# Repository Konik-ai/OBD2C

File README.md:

Designed using Kicad 8

Unlike harness box, OBD2-C doesn't use the relay. 

The purpose of it is to sniff CAN buses that are already present in OBD-2 port, similar to what white panda was doing in the past, but compatible with [OBD-C](https://github.com/commaai/neo/blob/master/car_harness/OBD-C.sch.pdf), though often only diagnostic CAN is populated on OBD-2.

The device exposes three CAN buses out of OBD-C:
- CAN0 (3, 11)
- CAN1 is routed to the JST (pin 2,3) connector (can be connected .e.g to [StepperServoCAN](https://github.com/dzid26/StepperServo-hardware)) and has optional 120ohm termination resistor (see jumpers).
Alternatively, bus 1 can be rerouted using jumpers as a GMLAN (obd pin 1) as in [white panda](https://comma-ai.medium.com/a-panda-and-a-cabana-how-to-get-started-car-hacking-with-comma-ai-b5e46fae8646) - but unlike [white panda](https://github.com/martiinezz/panda/blob/master/white-hw/README.md) it uses single wire [hack](https://canhacker.com/examples/gm-lan-single-wire-can-examples/) and is not tested
- CAN2 (pins 12, 13)
- CAN3 (pins 6, 14) - this one can be used e.g. as "[ELM327](https://github.com/commaai/panda/blob/master/examples/query_vin_and_stats.py)" or [vin](https://github.com/commaai/openpilot/blob/master/selfdrive/debug/car/vin.py) reading in openpilot 

As seen from PCB side

Some notes regarding openpilot bus names mapping to STM32 peripherals and [harness](https://github.com/commaai/neo/blob/master/car_harness/v1/open_pinout.sch.pdf) - (the indexes are not always consistent):
`HARNESS_STATUS_NORMAL`
| openpilot | STM32F4 | Harness |  WhitePanda 
| ---|---|---|---|
|sbu1|   | sbu2|  |
|sbu2|   | sbu1|  |
| bus 0  | CAN1 |  CAN0  | CAN1|
| bus 1  | CAN2 |  CAN1  | CAN2 |
|bus 1(obd)| CAN2 alt| CAN3| GMLAN|
| bus 2  | CAN3 | CAN2 | CAN3|

`HARNESS_STATUS_FLIPPED`
| openpilot | STM32F4 | Harness |  WhitePanda 
| ---|---|---|---|
|sbu1|   | sbu1|  |
|sbu2|   | sbu2|  |
| bus 0  | CAN3     |  CAN0  | CAN1|
| bus 1  | CAN2 alt|  CAN1  | CAN2 |
|bus 1(obd)| CAN2      | CAN3   | GMLAN|
| bus 2  | CAN1     | CAN2   | CAN3|

`+obd` means `set_obd_multiplexing(True)` in openpilot aka `panda.set_obd(True)` in panda lib aka `set_can_mode(CAN_MODE_OBD_CAN2)` in panda firmware.

Confusing? Yes. 
Especially inside panda [firmware](https://github.com/commaai/panda/pull/1860).

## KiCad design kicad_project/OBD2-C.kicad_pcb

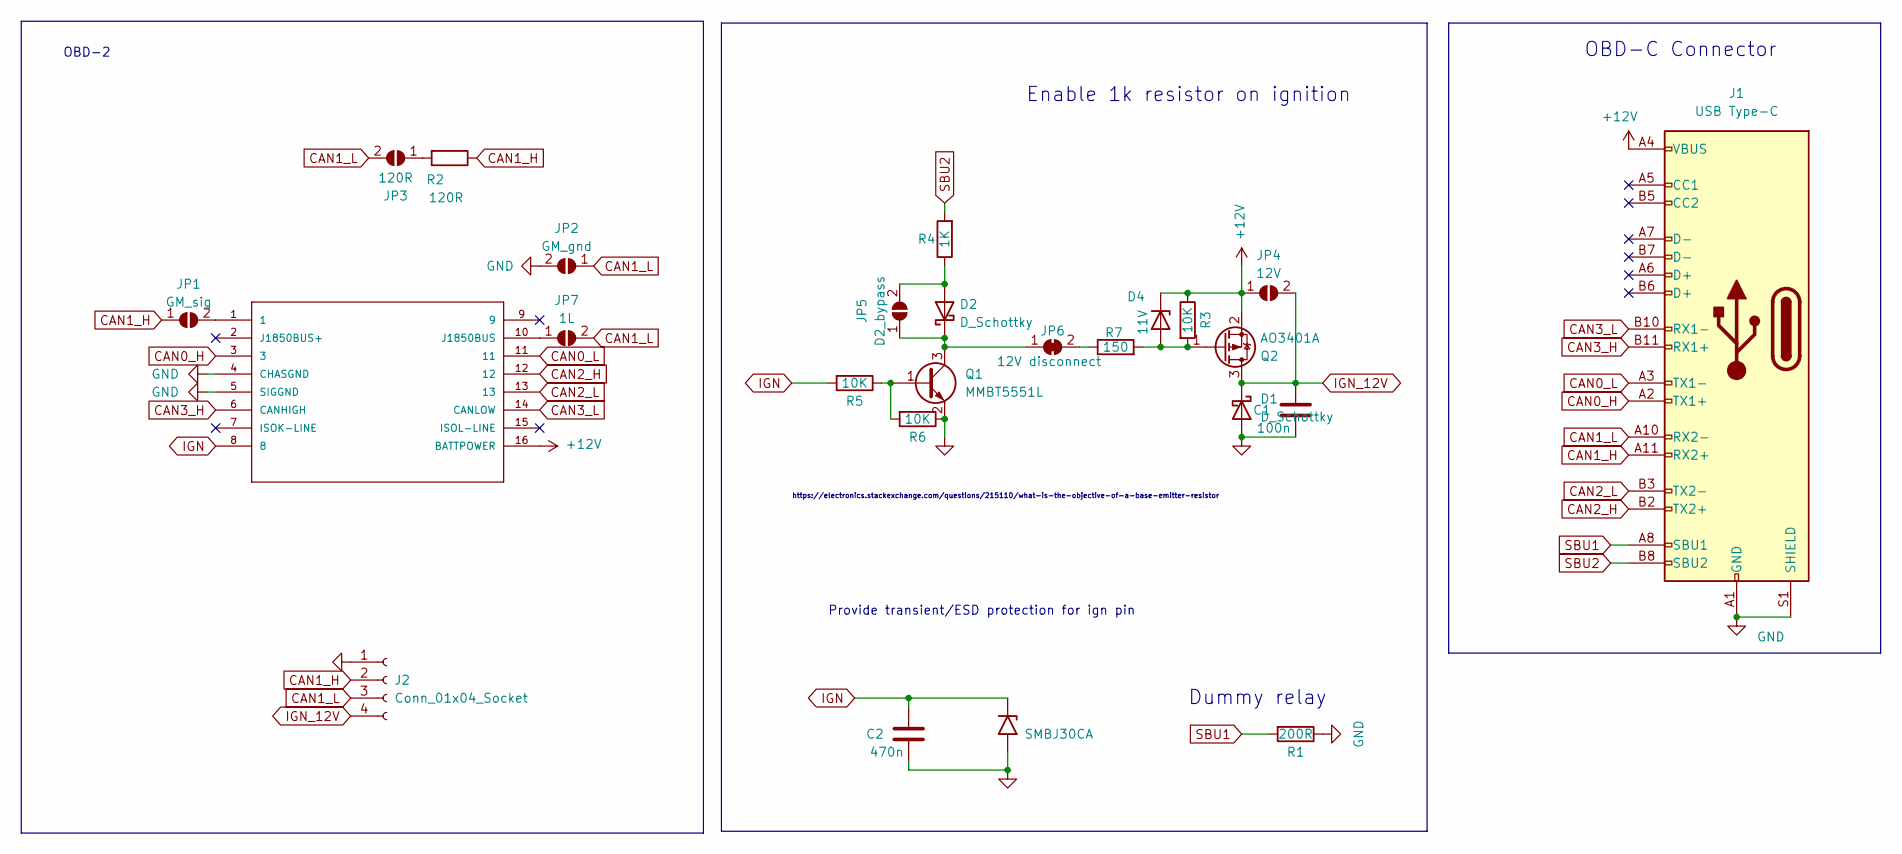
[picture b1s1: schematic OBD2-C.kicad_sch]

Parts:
C1: 100n; C_0603_1608Metric; Part CL21B474KBFNNNE; LCSC C14663
C2: 470n; C_0805_2012Metric; Part CL21B474KBFNNNE; LCSC C13967
D1, D2: D_Schottky; D_SOD-323; LCSC C64886
D3: SMBJ30CA; D_SOD-123F; LCSC C2990493
D4: 11V; D_SOD-123; LCSC C2932743
J1: USB Type-C; USB_C_Receptacle_GCT_USB4115-03-C; LCSC C2689742
J2: Conn_01x04_Socket; LCSC C566013
JP1: GM_sig; SolderJumper-2_P1.3mm_Open_TrianglePad1.0x1.5mm
JP2: GM_gnd; SolderJumper-2_P1.3mm_Open_TrianglePad1.0x1.5mm
JP3: 120R; SolderJumper-2_P1.3mm_Open_TrianglePad1.0x1.5mm
JP4: 12V; SolderJumper-2_P1.3mm_Open_TrianglePad1.0x1.5mm
JP5: D2_bypass; SolderJumper-2_P1.3mm_Open_RoundedPad1.0x1.5mm
JP6: 12V disconnect; SolderJumper-2_P1.3mm_Bridged_RoundedPad1.0x1.5mm
JP7: 1L; SolderJumper-2_P1.3mm_Open_TrianglePad1.0x1.5mm
M1: OBDII
Q1: MMBT5551L; SOT-23; LCSC C2145
Q2: AO3401A; SOT-23; LCSC C15127
R1: 200R; R_0805_2012Metric; LCSC C17540
R2: 120R; R_1206_3216Metric_Pad1.30x1.75mm_HandSolder; LCSC C17909
R3, R5, R6: 10K; R_0402_1005Metric; LCSC C25744
R4: 1K; R_0603_1608Metric; LCSC C21190
R7: 150; R_0603_1608Metric; LCSC C22808

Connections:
+12V: D4.1 (K), J1.A4 (VBUS), J1.A9 (VBUS), J1.B4 (VBUS), J1.B9 (VBUS), JP4.1 (A), M1.16 (BATTPOWER), Q2.2 (S), R3.1
CAN0_H: J1.A2 (TX1+), M1.3
CAN0_L: J1.A3 (TX1-), M1.11
CAN1_H: J1.A11 (RX2+), J2.2, JP1.1 (A), R2.1
CAN1_L: J1.A10 (RX2-), J2.3, JP2.1 (A), JP3.2 (B), JP7.2 (B)
CAN2_H: J1.B2 (TX2+), M1.12
CAN2_L: J1.B3 (TX2-), M1.13
CAN3_H: J1.B11 (RX1+), M1.6 (CANHIGH)
CAN3_L: J1.B10 (RX1-), M1.14 (CANLOW)
GND: C1.2, C2.2, D1.2 (A), D3.2 (A2), J1.A1 (GND), J1.A12 (GND), J1.B1 (GND), J1.B12 (GND), J1.S1 (SHIELD), J2.1, JP2.2 (B), M1.4 (CHASGND), M1.5 (SIGGND), Q1.2 (E), R1.1, R6.1
IGN: C2.1, D3.1 (A1), M1.8, R5.2
IGN_12V: C1.1, D1.1 (K), J2.4, JP4.2 (B), Q2.3 (D)
unnamed: D2.2 (A), JP5.2 (B), R4.1
unnamed: D2.1 (K), JP5.1 (A), JP6.1 (A), Q1.3 (C)
unnamed: D4.2 (A), Q2.1 (G), R3.2, R7.2
unnamed: JP1.2 (B), M1.1
unnamed: JP3.1 (A), R2.2
unnamed: JP6.2 (B), R7.1
unnamed: JP7.1 (A), M1.10 (J1850BUS)
unnamed: Q1.1 (B), R5.1, R6.2
SBU1: J1.A8 (SBU1), R1.2
SBU2: J1.B8 (SBU2), R4.2

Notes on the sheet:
OBD-2
OBD-C Connector
https://electronics.stackexchange.com/questions/215110/what-is-the-objective-of-a-base-emitter-resistor
Dummy relay
Enable 1k resistor on ignition
Provide transient/ESD protection for ign pin

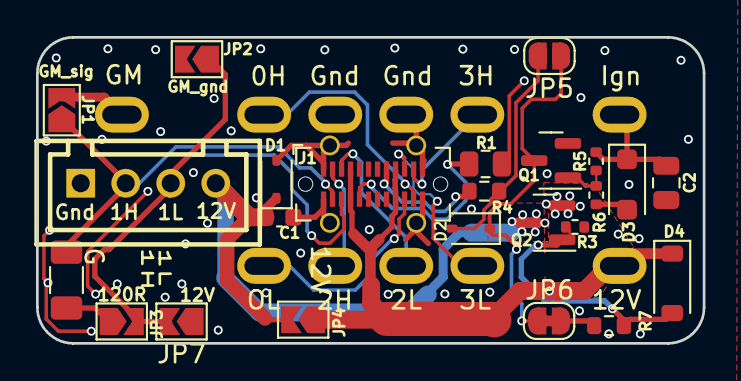
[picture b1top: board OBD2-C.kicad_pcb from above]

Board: 2 copper layers, 37.0 x 17.0 mm, 25 parts (1 on the bottom side), 21 nets.

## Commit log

2024-10-30 open-sourcing
2025-03-07 Jumpers, pinout
2025-03-07 Rotation
